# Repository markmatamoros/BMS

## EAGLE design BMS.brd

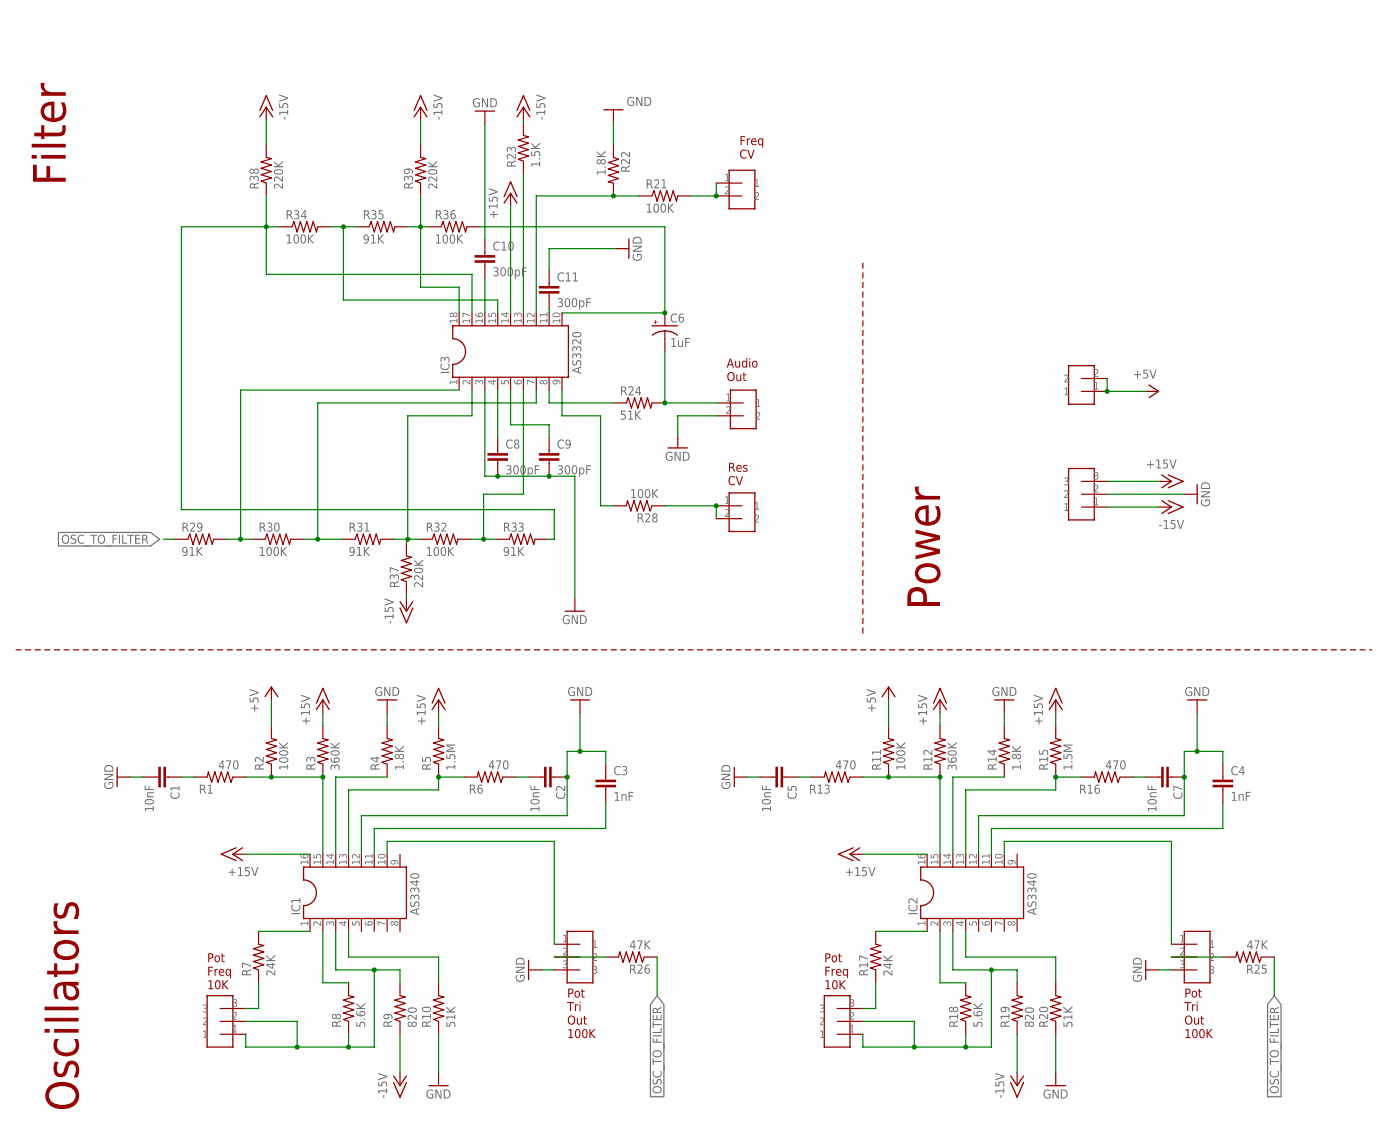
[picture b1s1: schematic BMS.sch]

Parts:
C1, C2, C5, C7: 10nF; 0805
C3, C4: 1nF; 0805
C6: 1uF; CAP_RADIAL_CAN_10MM
C8, C9, C10, C11: 300pF; 0805
IC1, IC2: AS3340; SOCKET-16
IC3: AS3320; SOCKET-18
R1, R6, R13, R16: 470; 0805
R2, R11, R21, R28, R30, R32, R34, R36: 100K; 0805
R3, R12: 360K; 0805
R4, R14, R22: 1.8K; 0805
R5, R15: 1.5M; 0805
R7, R17: 24K; 0805
R8, R18: 5.6K; 0805
R9, R19: 820; 0805
R10, R20, R24: 51K; 0805
R23: 1.5K; 0805
R25, R26: 47K; 0805
R29, R31, R33, R35: 91K; 0805
R37, R38, R39: 220K; 0805
U$1, U$4, U$6, U$8, U$10: HEADER-3-VERTICAL
U$2, U$3, U$13, U$14: HEADER-2-VERTICAL

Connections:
+5V: R2.2, R11.2, U$3.1, U$3.2
+15V: IC1.16, IC2.16, IC3.14, R3.2, R5.2, R12.2, R15.2, U$6.3
-15V: R9.1, R19.1, R23.2, R37.1, R38.2, R39.2, U$6.1
GND: C1.2, C2.1, C3.1, C4.1, C5.2, C7.1, C8.2, C9.2, C10.1, C11.1, IC1.12, IC2.12, IC3.3, R4.2, R10.1, R14.2, R20.1, R22.1, U$4.3, U$6.2, U$10.3, U$14.2
unnamed: C1.1, R1.2
unnamed: IC1.15, R1.1, R2.1, R3.1
unnamed: IC1.14, R4.1
unnamed: IC1.13, R5.1, R6.2
unnamed: C2.2, R6.1
unnamed: R26.2, U$4.2
unnamed: C3.2, IC1.11
unnamed: IC1.1, R7.2
unnamed: IC1.2, R8.2
unnamed: IC1.3, R8.1, R9.2, U$1.1, U$1.2
unnamed: IC1.4, R10.2
unnamed: IC3.13, R23.1
unnamed: R21.2, U$2.1, U$2.2
unnamed: R25.2, U$10.2
unnamed: R7.1, U$1.3
unnamed: IC1.10, U$4.1
unnamed: IC3.17, R33.2, R34.1, R38.1
unnamed: IC2.15, R11.1, R12.1, R13.1
unnamed: IC2.14, R14.1
unnamed: IC2.13, R15.1, R16.2
unnamed: C7.2, R16.1
unnamed: C4.2, IC2.11
unnamed: C5.1, R13.2
unnamed: IC2.1, R17.2
unnamed: IC2.2, R18.2
unnamed: IC2.3, R18.1, R19.2, U$8.1, U$8.2
unnamed: IC2.4, R20.2
unnamed: C9.1, IC3.5
unnamed: R17.1, U$8.3
unnamed: IC2.10, U$10.1
unnamed: C8.1, IC3.4
unnamed: C10.2, IC3.16
unnamed: C11.2, IC3.11
unnamed: IC3.12, R21.1, R22.2
unnamed: IC3.8, R24.1
unnamed: IC3.9, R28.2
unnamed: R28.1, U$13.1, U$13.2
unnamed: C6.-, R24.2, U$14.1
unnamed: C6.+, IC3.10, R36.2
unnamed: IC3.1, R29.2, R30.1
unnamed: IC3.7, R30.2, R31.1
unnamed: IC3.2, R31.2, R32.1, R37.2
unnamed: IC3.6, R32.2, R33.1
unnamed: IC3.15, R34.2, R35.1
unnamed: IC3.18, R35.2, R36.1, R39.1
OSC_TO_FILTER: R25.1, R26.1, R29.1

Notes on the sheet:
Pot Tri Out 100K
Pot Freq 10K
Res CV
Freq CV
Audio Out
Oscillators
Filter
Power

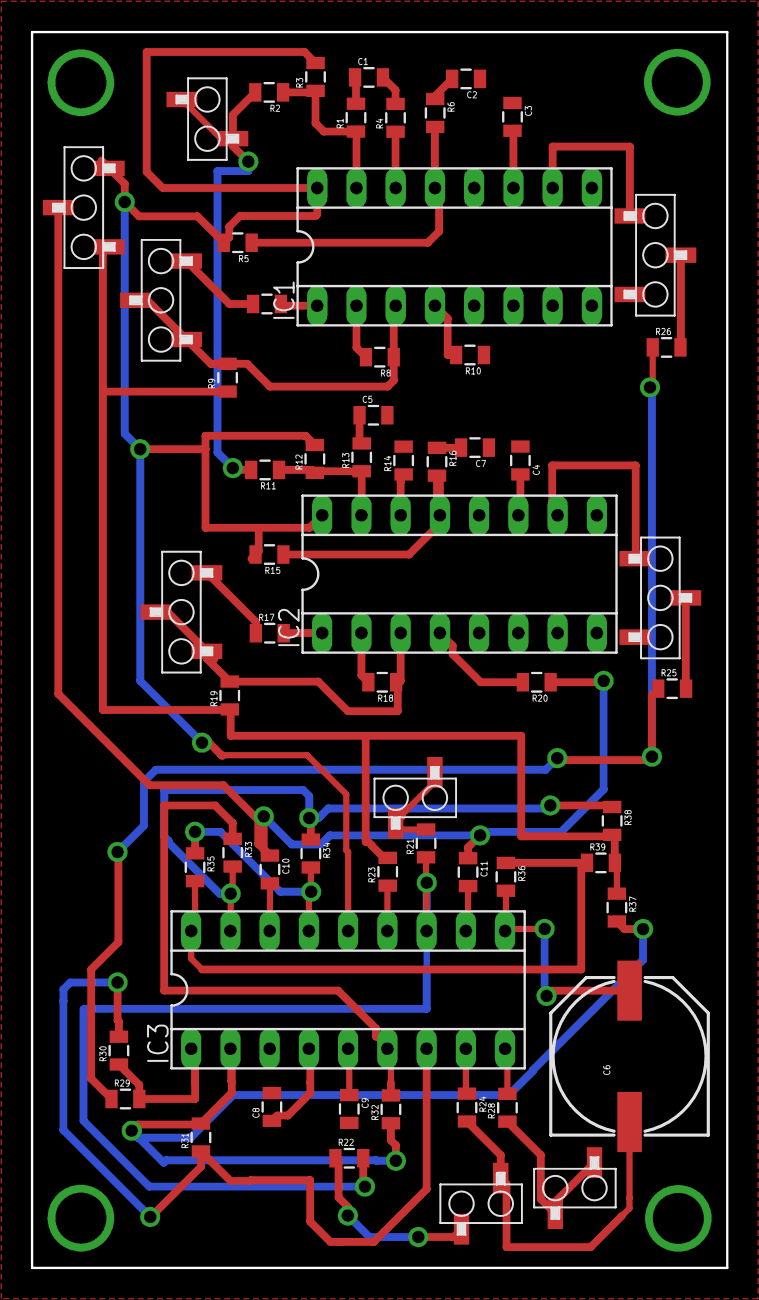
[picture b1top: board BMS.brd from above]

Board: 2 copper layers, 45.0 x 80.0 mm, 61 parts (0 on the bottom side), 50 nets.
